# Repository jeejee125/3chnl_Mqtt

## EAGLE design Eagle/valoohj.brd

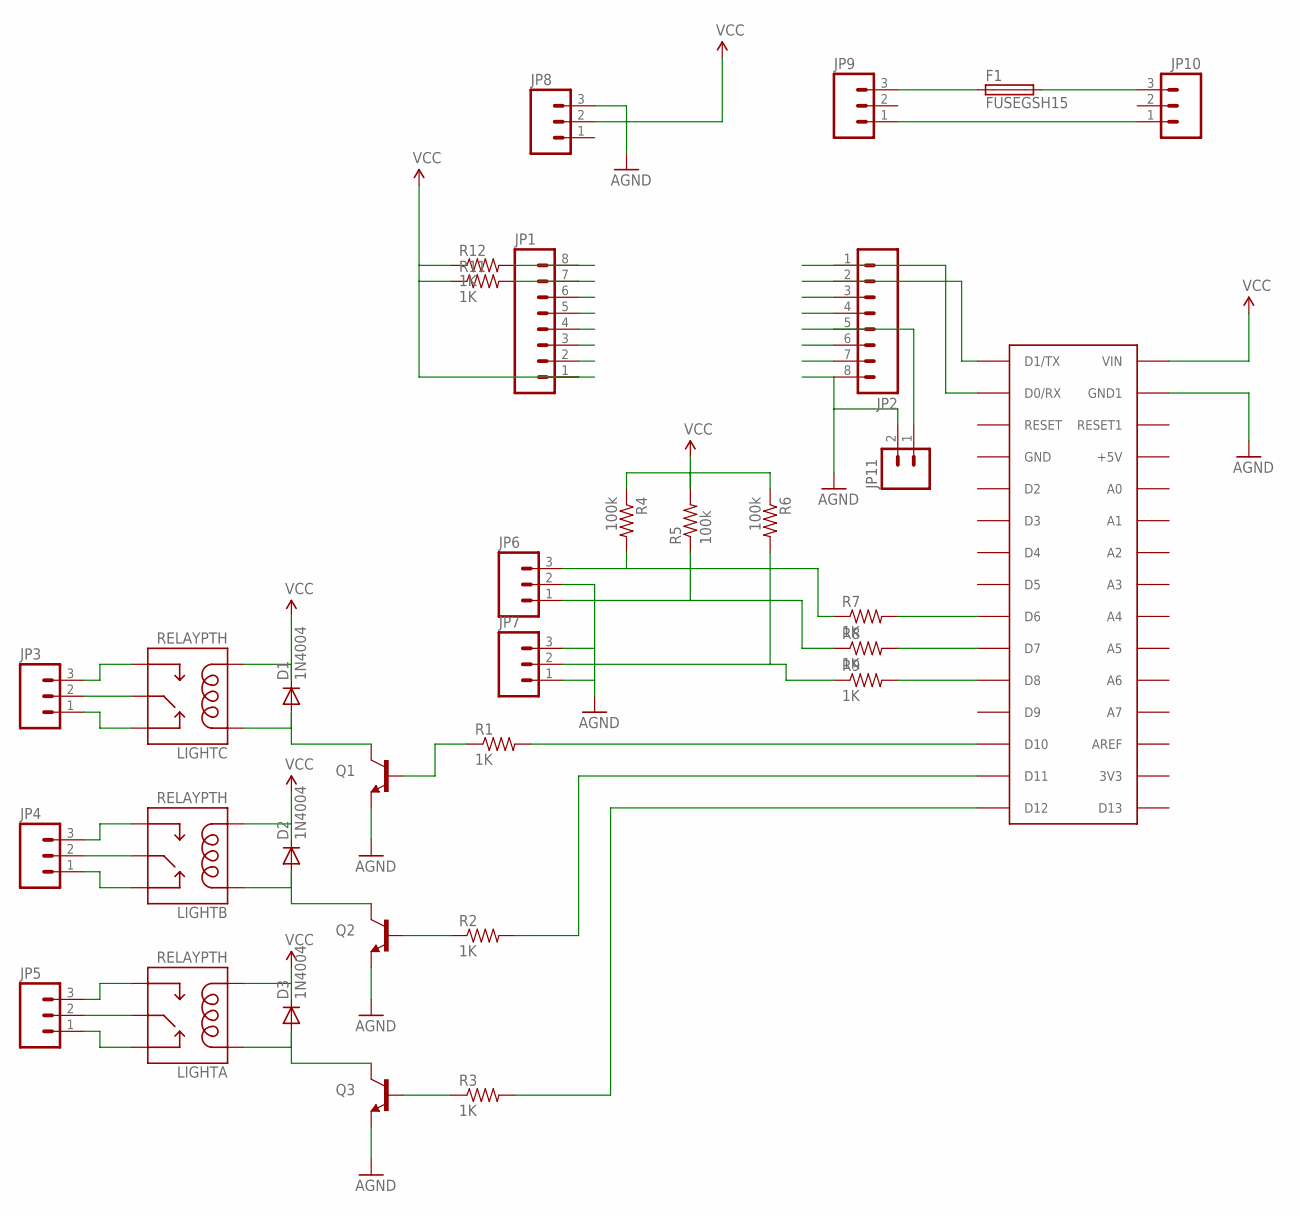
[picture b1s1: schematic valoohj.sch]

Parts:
D1, D2, D3: 1N4004; DO41-10
F1: FUSEGSH15; GSH15
JP1, JP2: M08LONGPADS; 1X08_LONGPADS
JP3, JP4, JP5, JP6, JP7: M03-SCREW-5MM; SCREWTERMINAL-5MM-3
JP8, JP9, JP10: M03SCREW; SCREWTERMINAL-3.5MM-3
JP11: M02LOCK; 1X02_LOCK
LIGHTA: RELAYPTH; SRD-05VDC-SL-C
LIGHTB: RELAYPTH; SRD-05VDC-SL-C
LIGHTC: RELAYPTH; SRD-05VDC-SL-C
Q1, Q2, Q3: TRANSISTOR_NPNBC547; TO-92-AMMO
R1, R2, R3, R7, R8, R9, R11, R12: 1K; AXIAL-0.3
R4, R5, R6: 100k; AXIAL-0.3
U$2: ARDUINONANO; PDIP-32

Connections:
AGND: JP2.8, JP6.2, JP7.1, JP7.3, JP8.3, JP11.2, Q1.3 (E), Q2.3 (E), Q3.3 (E), U$2.GND1
unnamed: R2.P$2 (2), U$2.D11
unnamed: F1.2, JP10.3
unnamed: F1.1, JP9.3
unnamed: JP9.1, JP10.1
unnamed: JP1.8, R12.P$2 (2)
unnamed: JP1.7, R11.P$2 (2)
unnamed: D1.A, LIGHTC.COIL1, Q1.1 (C)
unnamed: JP2.1, U$2.D0/RX
unnamed: JP2.2, U$2.D1/TX
unnamed: JP2.5, JP11.1
unnamed: D2.A, LIGHTB.COIL1, Q2.1 (C)
unnamed: R1.P$2 (2), U$2.D10
unnamed: Q1.2 (B), R1.P$1 (1)
unnamed: D3.A, LIGHTA.COIL1, Q3.1 (C)
unnamed: R9.P$2 (2), U$2.D8
unnamed: Q2.2 (B), R2.P$1 (1)
unnamed: Q3.2 (B), R3.P$1 (1)
unnamed: R3.P$2 (2), U$2.D12
unnamed: R8.P$2 (2), U$2.D7
unnamed: R7.P$2 (2), U$2.D6
unnamed: JP6.3, R4.P$2 (2), R7.P$1 (1)
unnamed: JP6.1, R5.P$1 (1), R8.P$1 (1)
unnamed: JP7.2, R6.P$2 (2), R9.P$1 (1)
unnamed: JP3.3, LIGHTC.SWOPEN
unnamed: JP3.2, LIGHTC.SWCOMMON
unnamed: JP3.1, LIGHTC.SWCLOSED (SWCLOSE)
unnamed: JP4.3, LIGHTB.SWOPEN
unnamed: JP4.2, LIGHTB.SWCOMMON
unnamed: JP4.1, LIGHTB.SWCLOSED (SWCLOSE)
unnamed: JP5.3, LIGHTA.SWOPEN
unnamed: JP5.2, LIGHTA.SWCOMMON
unnamed: JP5.1, LIGHTA.SWCLOSED (SWCLOSE)
VCC: D1.C, D2.C, D3.C, JP1.1, JP8.2, LIGHTA.COIL0, LIGHTB.COIL0, LIGHTC.COIL0, R4.P$1 (1), R5.P$2 (2), R6.P$1 (1), R11.P$1 (1), R12.P$1 (1), U$2.VIN

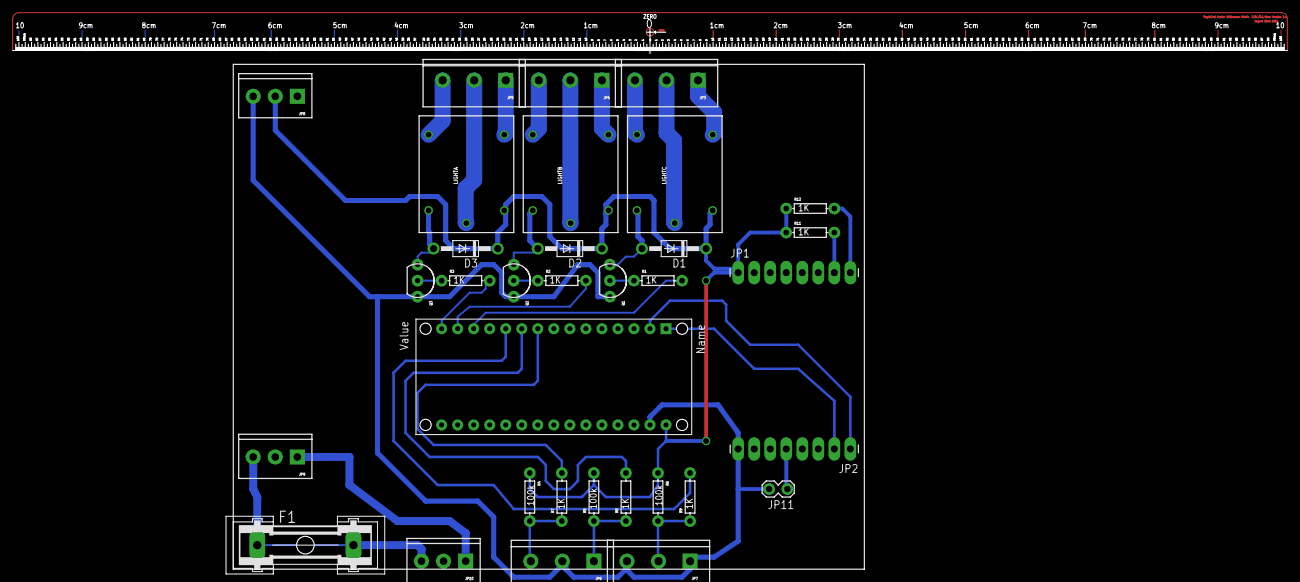
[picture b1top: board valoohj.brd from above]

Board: 2 copper layers, 100.0 x 80.0 mm, 34 parts (0 on the bottom side), 34 nets.

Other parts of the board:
U$4: RULER

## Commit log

2015-04-16 Firs Commit
2015-04-16 Second Commit

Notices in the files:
parts and their libraries:
SparkFun-Connectors: Licensing: Creative Commons ShareAlike 4.0 International - https://creativecommons.org/licenses/by-sa/4.0
